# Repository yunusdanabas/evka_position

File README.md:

# Evka Position: Spherical 3D Positioning Prototype

> Turkce operator guide: [README_TR.md](README_TR.md)

Evka Position is an existing-repository prototype that derives a 3D point from two rotary
encoders and one draw-wire encoder:

```text
encoder counts -> (radius, theta, phi) -> sensor-frame (X, Y, Z) mm
```

Start with [HANDOFF.md](HANDOFF.md), use [docs/ONBOARDING.md](docs/ONBOARDING.md) for the
self-contained setup and safety baseline, and browse [docs/README.md](docs/README.md) for the
documentation status index.

## Handoff Status

| Area | Approved statement |
|---|---|
| Current hardware | The assembled ESP32-S3 v4 carrier is the current prototype. It is not a production-qualified product. |
| Firmware | Shared classic/v4 firmware and all PlatformIO environments build successfully. No new flash or hardware validation is claimed. |
| Telemetry | Live 20 Hz telemetry has been observed in earlier work. Full end-to-end hardware acceptance remains open. |
| Repeatability | Theta count loss is unresolved. The recorded return error reached about 1.1 degrees, approximately 35 mm at 2 m. |
| Coordinates | Firmware and `tools/evka_gui` report the sensor frame. No endpoint/world transform has been accepted. |
| Host application | `tools/evka_gui` is the canonical operator GUI. The vendor C# application has been deleted; the TCP compatibility protocol remains supported. |
| Legal/release | The repository has no redistribution license and makes no public production-readiness claim. |

Do not hide theta slip, backlash, or lost counts by changing PPR or fitting a world transform.
Resolve repeatability first, then calibrate scale, fit a candidate transform, and validate it on
hold-out points.

Known repeatability record:
[docs/calibration/sessions/2026-07-17_repeatability.md](docs/calibration/sessions/2026-07-17_repeatability.md).

### Software Verification Record

| Check | Result |
|---|---|
| `QT_QPA_PLATFORM=offscreen pytest -q -m qt_heavy --forked` | PASS: 44 tests |
| `QT_QPA_PLATFORM=offscreen pytest -q -m "not qt_heavy"` | PASS: 160 tests, 11 subtests (204 total with the above) |
| Dashboard harness (`npm ci && npm test`) | PASS: 50 checks |
| `python -m compileall tools -q` | PASS |
| `python -m tools.ipt.solver` | PASS: 0.405 mm target error |
| PlatformIO build matrix | PASS: all 10 configured environments |

The Python suite runs as **two invocations on purpose**. Modules marked `qt_heavy` build
pyqtgraph widgets that segfault when they share a process, so they run forked; forking only
works if the parent has not built a QApplication first, which is why they get their own
invocation. A plain `pytest -q` is still expected to segfault intermittently — use the two
commands above. Background: [docs/CI_PYTEST_SEGFAULT_LOG.md](docs/CI_PYTEST_SEGFAULT_LOG.md).

These are software-only results. Hardware acceptance remains governed by the open
gates in [docs/integration/final_integration_validation.md](docs/integration/final_integration_validation.md).

## Hardware Baseline

- MCU: ESP32-S3-DevKitC-1 on the v4 carrier; classic Wemos D1 R32 remains a compatibility target.
- Theta/Phi: Autonics E40S6-5000, 20,000 counts/rev at X4 quadrature.
- Radius: OPKON DWEM2 P2000, theoretical 8,000 counts/rev at X4 quadrature.
- Main firmware encoder driver: `madhephaestus/ESP32Encoder` using ESP32 PCNT.
- Encoder outputs are 5 V; the v4 carrier includes the signal dividers required by the ESP32.

### v4 Connector Map

| Connector | Axis | PCB pin order | GPIO |
|---|---|---|---|
| J1 | Draw-wire | `1=A, 2=GND, 3=B, 4=+5V` | A=7, B=8 |
| J2 | Phi | `1=+5V, 2=A, 3=GND, 4=B` | A=4, B=5 |
| J3 | Theta | `1=A, 2=GND, 3=B, 4=+5V` | A=9, B=10 |

Cable colors:

| Encoder | A | B | +5V | GND |
|---|---|---|---|---|
| E40S6 theta/phi | Black | White | Brown | Blue |
| DWEM2 draw-wire | Yellow | Green | Brown | White |

This connector order is derived from the v4 KiCad PCB/pad nets and the current firmware pin map.
It was **not physically reverified during this final documentation pass**. Verify the actual board
and cable before applying power.

Compile-time pins, calibration defaults, battery behavior, LED selection, and network constants
are defined in `firmware/src/SphericalSensor.h`. Runtime PPR values may be overridden by NVS, so
query `CONSTANTS` before a calibration session.

## Canonical Operator GUI

The host-tools package is version `0.2.1` and requires Python 3.10 or newer.

Install the Python dependencies from the repository root:

```bash
python3 -m venv .venv
source .venv/bin/activate
pip install -r requirements.txt
```

Run the canonical GUI:

```bash
python -m tools.evka_gui
python -m tools.evka_gui --serial /dev/ttyACM0 --baud 115200
python -m tools.evka_gui --tcp 192.168.1.50:8080
python -m tools.evka_gui --ws 192.168.1.50
python -m tools.evka_gui --replay frames.csv
```

`evka_gui` supports Serial, TCP, WebSocket, and replay; includes Quick IPT, diagnostics,
recording, snapshots, and the calibration-report workflow; and records raw sensor-frame data.
Software zero is a display/session offset only. The GUI does not apply an endpoint/world transform
to live telemetry, so its XYZ and IPT results remain in the sensor frame.

The standalone `tools/position_checker` entry points are legacy compatibility tools.

## Firmware Build and Flash

PlatformIO is the supported firmware toolchain. Build without uploading:

```bash
pio run -e esp32s3_v4
pio run -e wemos_d1_r32
pio run -e button_remote
```

Flash after wiring and safety review. Replace `/dev/ttyACM0` with the correct port
(`/dev/ttyUSB0` on some boards, `COMx` on Windows). Do not open the same port in two apps at once.

**Main device** (ESP32-S3 v4 carrier — current prototype):

```bash
pio run -e esp32s3_v4 --target upload --upload-port /dev/ttyACM0
pio device monitor -e esp32s3_v4
```

Classic Wemos compatibility target (not for the v4 carrier):

```bash
pio run -e wemos_d1_r32 --target upload --upload-port /dev/ttyUSB0
```

**Remote control** (ESP32-C3 pendant, ESP-NOW):

```bash
pio run -e button_remote --target upload --upload-port /dev/ttyACM0
pio device monitor -e button_remote
```

Bench-only pendant test firmware (own AP `REMOTE_TEST`, no ESP-NOW — see
[`tools/remote_tester/README.md`](tools/remote_tester/README.md)):

```bash
pio run -e button_remote_test --target upload --upload-port /dev/ttyACM0
```

The `test_*` environments use the classic Wemos pin map and must not be flashed onto the v4
carrier. See [CONTRIBUTING.md](CONTRIBUTING.md) and
[pcb_design/EVKA_position_v4/FIRMWARE.md](pcb_design/EVKA_position_v4/FIRMWARE.md) before any
flash or bring-up work.

## Protocol and Networking

The canonical, source-derived transport and command reference is
**[docs/PROTOCOL.md](docs/PROTOCOL.md)**. In summary:

- Serial: 115200 baud; machine-readable `DATA,...` at 20 Hz.
- WebSocket: `ws://<device>/ws`; `DATA,...` at 20 Hz.
- TCP: port 8080; separate `X...,Y...,Z...` and `SENSOR,...` lines at 20 Hz.
- `RAW_COUNTS` returns zero-relative counts, not absolute PCNT values.

The firmware's existing credentials and addresses are unchanged:

| Setting | Current value |
|---|---|
| AP SSID | `CMDCNC_EVKA` |
| AP password | `cmdcnc1234` |
| AP dashboard | `http://192.168.1.50` |
| TCP | `192.168.1.50:8080` |
| WebSocket | `ws://192.168.1.50/ws` |
| STA static profile | `192.168.1.84/24`, gateway `192.168.1.254` |
| STA default network | `WIFI_STA_DEFAULT_SSID` / `_PASS` in [firmware/src/SphericalSensor.h](firmware/src/SphericalSensor.h) — a specific shop-floor network; change before deploying elsewhere |

These fixed credentials and unauthenticated command channels are suitable only for an isolated,
trusted lab network. Do not expose the AP, TCP port, or WebSocket to an untrusted LAN or the public
internet. `WIFI_SET` changes stored STA credentials and reboots the device.

## Calibration Boundary

The active workflow is documented under [docs/calibration/](docs/calibration/). No shared/default
calibration JSON is checked in and no endpoint/world transform is accepted. After the repeatability,
calibration, and hold-out gates pass, a session JSON may be supplied explicitly to the legacy
visualizer with `--legacy-visualizer --calibration <session-calibration.json>`. The canonical
`tools/evka_gui` remains sensor-frame-only.

## Repository Areas

- Active: `firmware/src/`, `tools/evka_gui/`, `docs/PROTOCOL.md`, active calibration and v4 docs.
- Archive/reference: classic test material, integration history, GUI migration logs, and
  `docs/hardware_design/12v_legacy/`.
- Research: `laser_radius/` and `docs/research/`; these are studies, not implemented baseline.
- Unindexed: `report/` holds a standalone LaTeX report that nothing else references. It is kept
  for the record and is not part of the documentation status index.

Prebuilt operator GUI bundles (Windows `.exe` and portable source) are published as assets on the
[v0.2.1 release](https://github.com/yunusdanabas/evka_position/releases/tag/v0.2.1), not in git.
Rebuild them with the scripts in `packaging/evka_gui/`.

## License and Redistribution

There is no repository license file. Default copyright restrictions apply. Do not redistribute,
publish a product release, or represent this prototype as production-ready until ownership and
licensing are explicitly resolved. Historical vendor C# material has been deleted; that cleanup does
not affect the retained TCP wire protocol.

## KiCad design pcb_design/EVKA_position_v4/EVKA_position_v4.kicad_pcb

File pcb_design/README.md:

# pcb_design — KiCad workspaces

Four board revisions live side by side. **Only v4 is fabricated and current** —
the rest are kept for reference.

| Workspace | Status | Notes |
|---|---|---|
| `EVKA_position_v4/` | **CURRENT — fabricated** | ESP32-S3-DevKitC-1 carrier; firmware env `esp32s3_v4` (`-DPCB_V4`). Pin map, bring-up, battery, LED: [`EVKA_position_v4/FIRMWARE.md`](EVKA_position_v4/FIRMWARE.md) |
| `EvkaPosition_v2/` | Superseded | Full-featured 5V design (74HC14 buffers, load-sharing). ERC-clean but never fabricated. Its design docs were removed on migration to v4 — recover from git history if needed |
| `EVKA_position_v3/` | Superseded | Stripped "simple" variant of v2 (direct-GPIO dividers, no buffers). Never fabricated |
| `EVKA_position_v5/` | Experimental / WIP | Layout exploration after v4; not fabricated, no firmware support |

Netlists are generated files — regenerate with
`kicad-cli sch export netlist <project>.kicad_sch` (a stray root-level
`EvkaPosition_v2.net` is git-ignored for this reason). KiCad backup folders
(`*-backups/`) are git-ignored too.

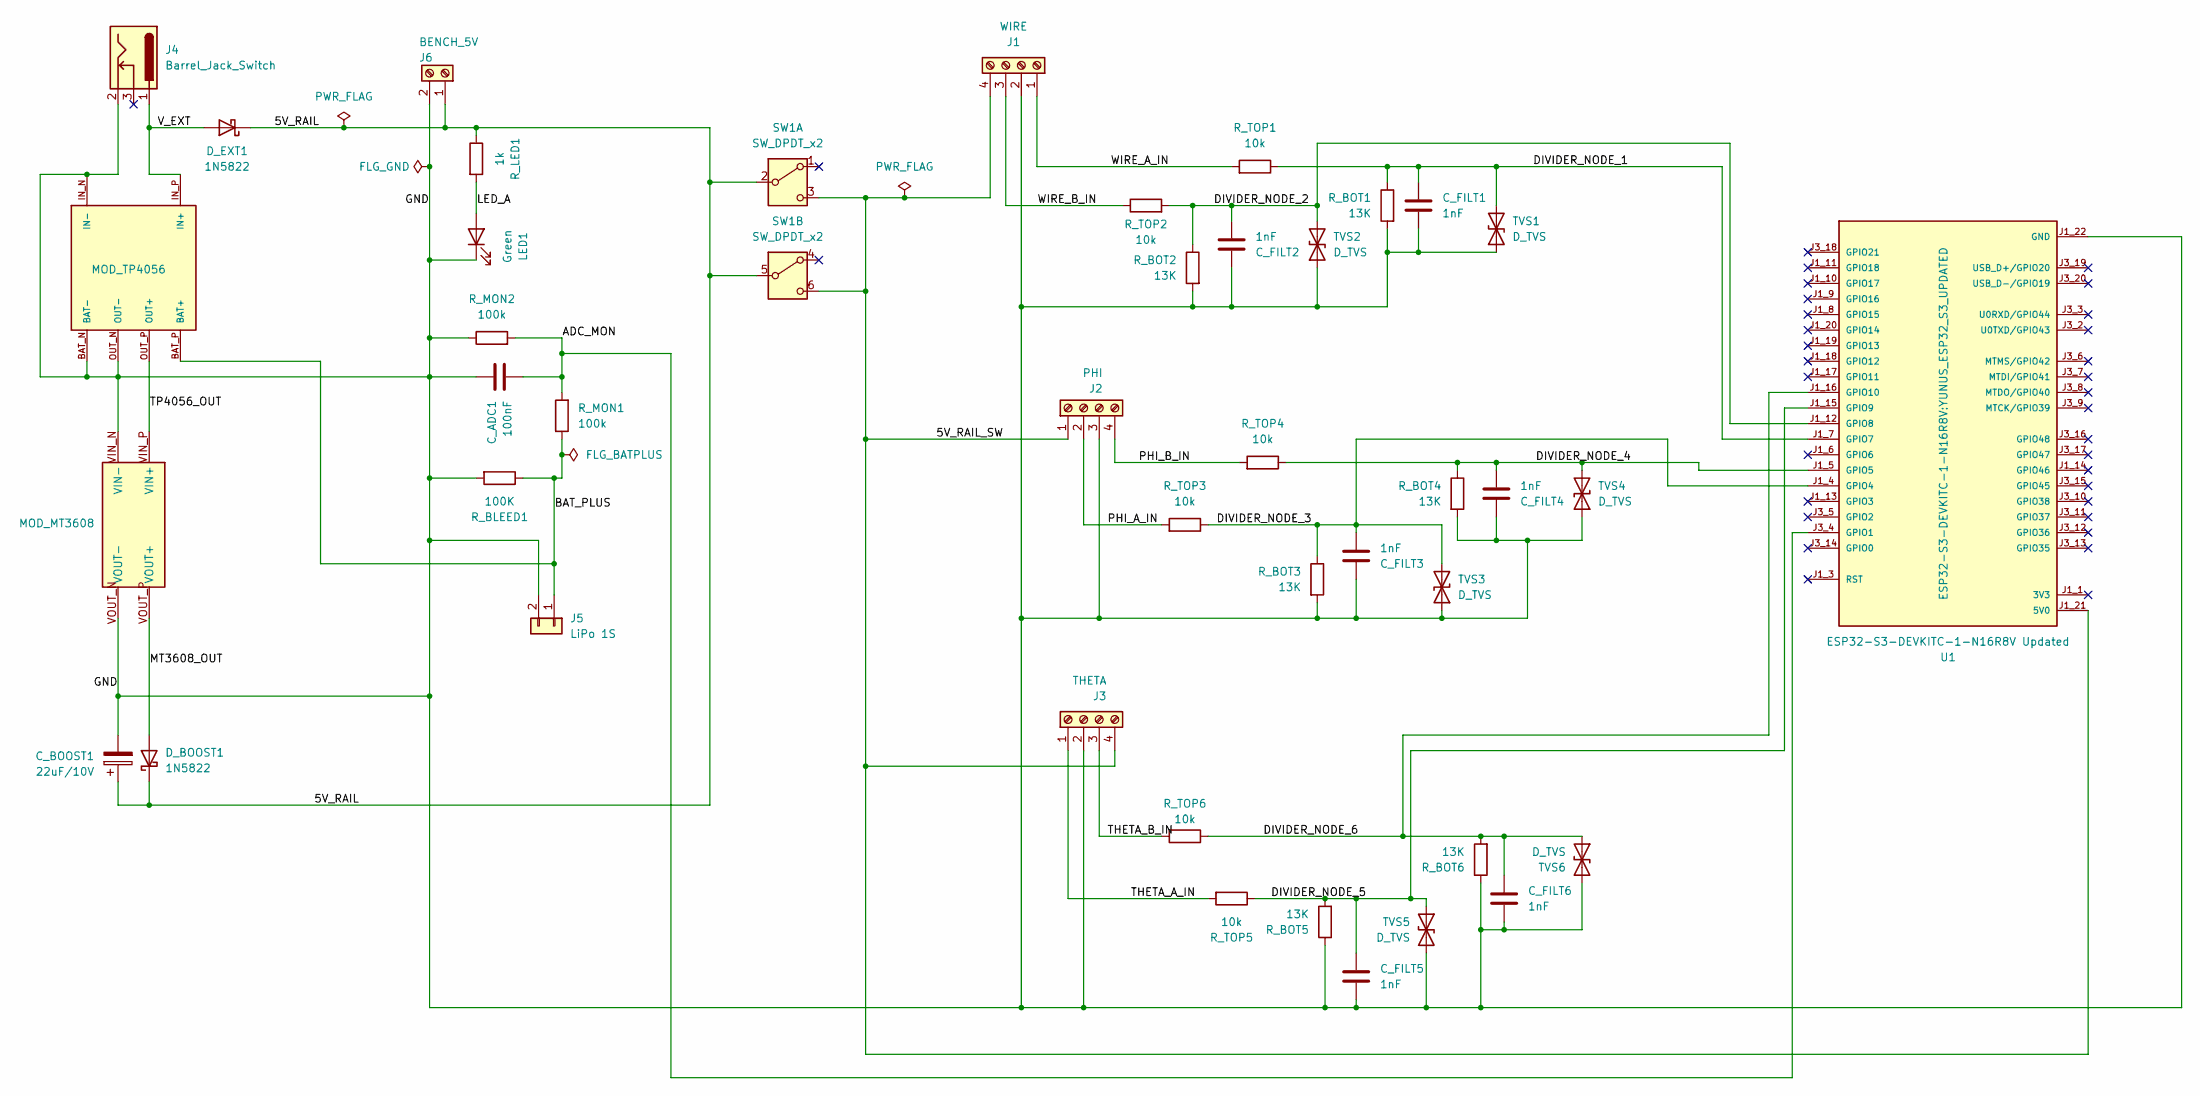
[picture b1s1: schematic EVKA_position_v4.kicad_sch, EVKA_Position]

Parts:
C_ADC1: 100nF; C_Disc_D5.0mm_W2.5mm_P5.00mm
C_BOOST1: 22uF/10V; CP_Radial_D5.0mm_P2.50mm
C_FILT1, C_FILT2, C_FILT3, C_FILT4, C_FILT5, C_FILT6: 1nF; C_Disc_D5.0mm_W2.5mm_P5.00mm
D_BOOST1: 1N5822; D_DO-201AD_P15.24mm_Horizontal
D_EXT1: 1N5822; D_DO-201AD_P15.24mm_Horizontal
J1: WIRE; TerminalBlock_Phoenix_MKDS-1,5-4_1x04_P5.00mm_Horizontal
J2: PHI; TerminalBlock_Phoenix_MKDS-1,5-4_1x04_P5.00mm_Horizontal
J3: THETA; TerminalBlock_Phoenix_MKDS-1,5-4_1x04_P5.00mm_Horizontal
J4: Barrel_Jack_Switch; BarrelJack_CUI_PJ-102AH_Horizontal
J5: LiPo 1S; JST_PH_B2B-PH-K_1x02_P2.00mm_Vertical
J6: BENCH_5V; TerminalBlock_Phoenix_MKDS-1,5-2_1x02_P5.00mm_Horizontal
LED1: Green; LED_D5.0mm
MOD_MT3608: MT3608 Updated; MODULE_MT3608_DC-DC_STEP_UP_CONVERTER_2A_BOOSTER_MODULE
MOD_TP4056: TP4056_MICRO-USB_CHARGER_-_1A; MODULE_TP4056_MICRO-USB_CHARGER_-_1A
R_BLEED1: 100K; R_Axial_DIN0207_L6.3mm_D2.5mm_P7.62mm_Horizontal
R_BOT1, R_BOT2, R_BOT3, R_BOT4, R_BOT5, R_BOT6: 13K; R_Axial_DIN0207_L6.3mm_D2.5mm_P7.62mm_Horizontal
R_LED1: 1k; R_Axial_DIN0207_L6.3mm_D2.5mm_P7.62mm_Horizontal
R_MON1, R_MON2: 100k; R_Axial_DIN0207_L6.3mm_D2.5mm_P7.62mm_Horizontal
R_TOP1, R_TOP2, R_TOP3, R_TOP4, R_TOP5, R_TOP6: 10k; R_Axial_DIN0207_L6.3mm_D2.5mm_P7.62mm_Horizontal
SW1: SW_DPDT_x2; SW_NKK_G1xJP
TVS1, TVS2, TVS3, TVS4, TVS5, TVS6: D_TVS; D_DO-35_SOD27_P7.62mm_Horizontal
U1: ESP32-S3-DEVKITC-1-N16R8V Updated; YUNUS_ESP32_S3_UPDATED; PARTREV 1.1

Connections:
/5V_RAIL: C_BOOST1.1, D_BOOST1.1 (K), D_EXT1.1 (K), J6.1, R_LED1.1, SW1.2 (B), SW1.5 (B)
/5V_RAIL_SW: J1.4, J2.1, J3.4, SW1.3 (C), SW1.6 (C), U1.J1_21 (5V0)
/ADC_MON: C_ADC1.2, R_MON1.2, R_MON2.2, U1.J3_4 (GPIO1)
/BAT_PLUS: J5.1, MOD_TP4056.BAT_P (BAT+), R_BLEED1.1, R_MON1.1
/DIVIDER_NODE_1: C_FILT1.1, R_BOT1.1, R_TOP1.1, TVS1.2 (A2), U1.J1_7 (GPIO7)
/DIVIDER_NODE_2: C_FILT2.2, R_BOT2.1, R_TOP2.2, TVS2.2 (A2), U1.J1_12 (GPIO8)
/DIVIDER_NODE_3: C_FILT3.2, R_BOT3.1, R_TOP3.1, TVS3.2 (A2), U1.J1_4 (GPIO4)
/DIVIDER_NODE_4: C_FILT4.2, R_BOT4.1, R_TOP4.1, TVS4.2 (A2), U1.J1_5 (GPIO5)
/DIVIDER_NODE_5: C_FILT5.1, R_BOT5.2, R_TOP5.1, TVS5.1 (A1), U1.J1_15 (GPIO9)
/DIVIDER_NODE_6: C_FILT6.1, R_BOT6.2, R_TOP6.1, TVS6.1 (A1), U1.J1_16 (GPIO10)
/LED_A: LED1.2 (A), R_LED1.2
/MT3608_OUT: D_BOOST1.2 (A), MOD_MT3608.VOUT_P (VOUT+)
/PHI_A_IN: J2.2, R_TOP3.2
/PHI_B_IN: J2.4, R_TOP4.2
/THETA_A_IN: J3.1, R_TOP5.2
/THETA_B_IN: J3.3, R_TOP6.2
/TP4056_OUT: MOD_MT3608.VIN_P (VIN+), MOD_TP4056.OUT_P (OUT+)
/V_EXT: D_EXT1.2 (A), J4.1, MOD_TP4056.IN_P (IN+)
/WIRE_A_IN: J1.1, R_TOP1.2
/WIRE_B_IN: J1.3, R_TOP2.1
GND: C_ADC1.1, C_BOOST1.2, C_FILT1.2, C_FILT2.1, C_FILT3.1, C_FILT4.1, C_FILT5.2, C_FILT6.2, J1.2, J2.3, J3.2, J4.2, J5.2, J6.2, LED1.1 (K), MOD_MT3608.VIN_N (VIN-), MOD_MT3608.VOUT_N (VOUT-), MOD_TP4056.BAT_N (BAT-), MOD_TP4056.IN_N (IN-), MOD_TP4056.OUT_N (OUT-), R_BLEED1.2, R_BOT1.2, R_BOT2.2, R_BOT3.2, R_BOT4.2, R_BOT5.1, R_BOT6.1, R_MON2.1, TVS1.1 (A1), TVS2.1 (A1), TVS3.1 (A1), TVS4.1 (A1), TVS5.2 (A2), TVS6.2 (A2), U1.J1_22 (GND), U1.J3_1 (GND), U1.J3_21 (GND), U1.J3_22 (GND)

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
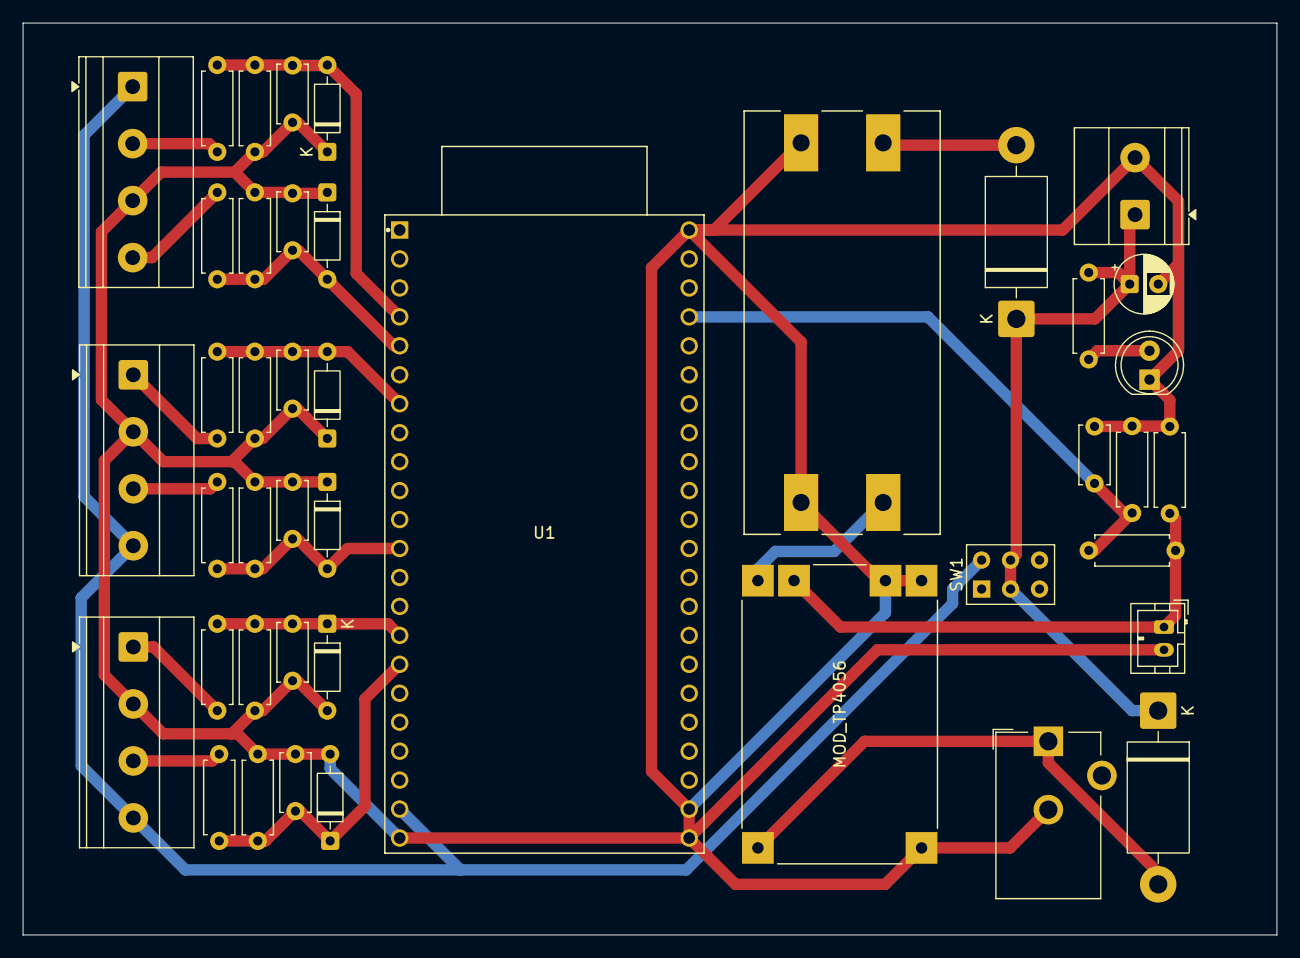
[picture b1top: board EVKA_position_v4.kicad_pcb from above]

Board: 2 copper layers, 110.0 x 80.0 mm, 43 parts (0 on the bottom side), 21 nets.

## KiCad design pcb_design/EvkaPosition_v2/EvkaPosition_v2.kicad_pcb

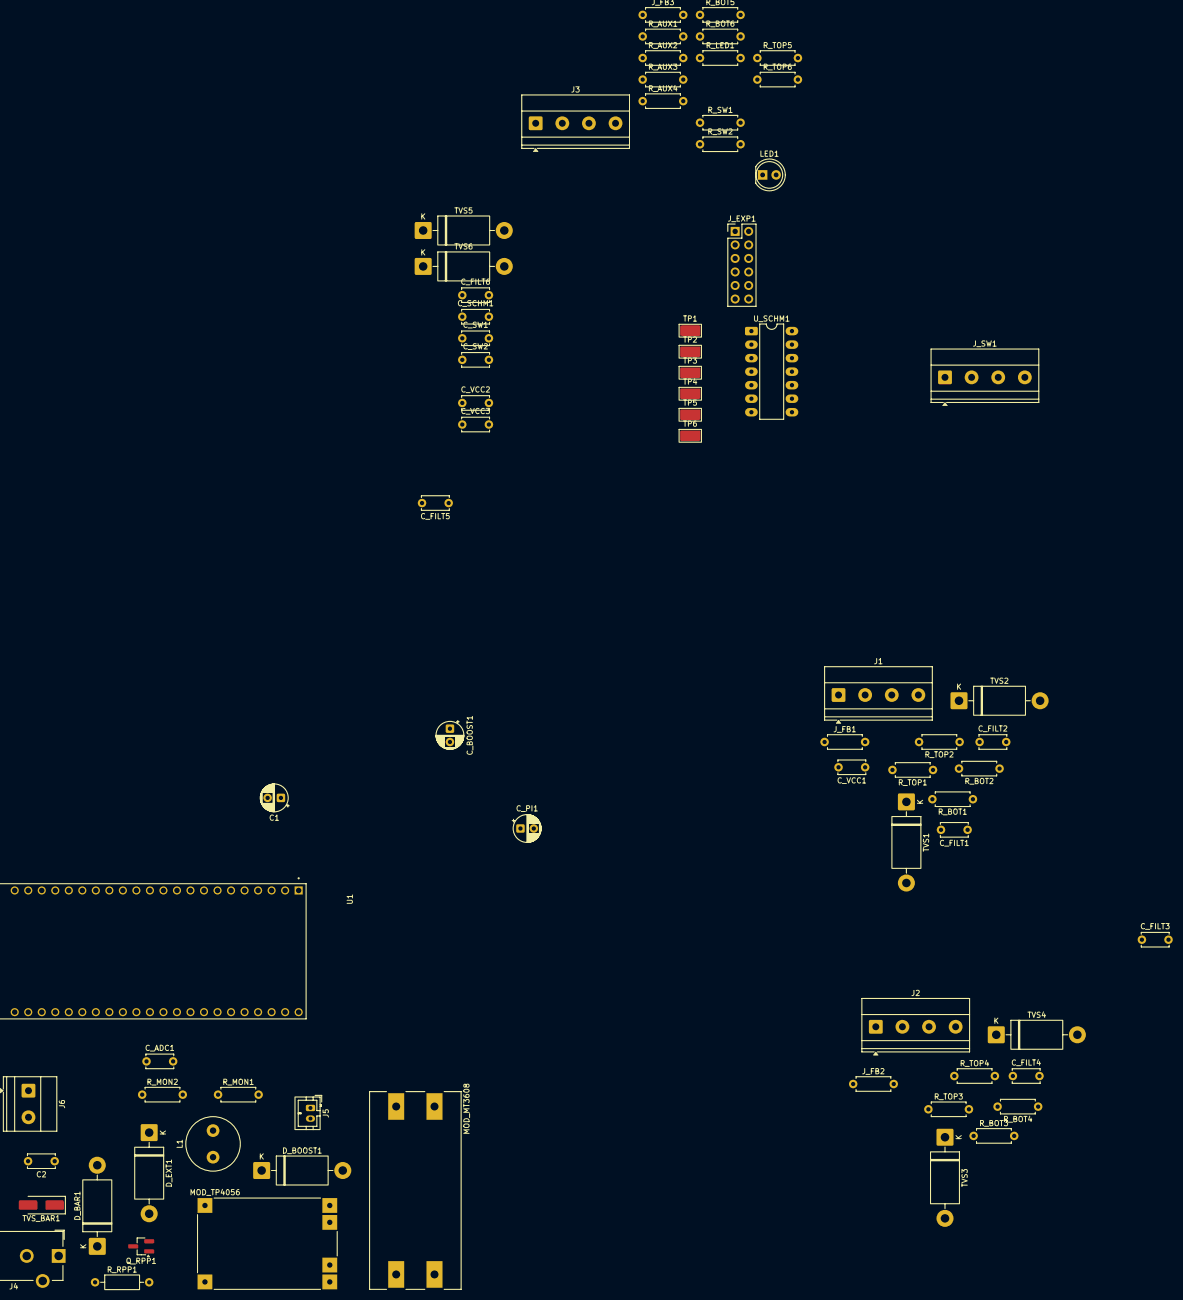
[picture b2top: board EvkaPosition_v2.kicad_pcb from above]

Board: 2 copper layers, 73 parts (0 on the bottom side), 44 nets, no tracks yet.

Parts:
C1: 220uF/10V; CP_Radial_D5.0mm_P2.50mm
C2: 100nF; C_Disc_D5.0mm_W2.5mm_P5.00mm
C_ADC1: 100nF; C_Disc_D5.0mm_W2.5mm_P5.00mm
C_BOOST1: 22uF/10V; CP_Radial_D5.0mm_P2.50mm
C_FILT1, C_FILT2, C_FILT3, C_FILT4, C_FILT5, C_FILT6: 10nF; C_Disc_D5.0mm_W2.5mm_P5.00mm
C_PI1: 10uF/10V; CP_Radial_D5.0mm_P2.50mm
C_SCHM1: 100nF; C_Disc_D5.0mm_W2.5mm_P5.00mm
C_SW1, C_SW2: 100nF; C_Disc_D5.0mm_W2.5mm_P5.00mm
C_VCC1, C_VCC2, C_VCC3: 100nF; C_Disc_D5.0mm_W2.5mm_P5.00mm
D_BAR1: 1N5822; D_DO-201AD_P15.24mm_Horizontal
D_BOOST1: 1N5822; D_DO-201AD_P15.24mm_Horizontal
D_EXT1: 1N5822; D_DO-201AD_P15.24mm_Horizontal
J1: THETA; TerminalBlock_Phoenix_MKDS-1,5-4_1x04_P5.00mm_Horizontal
J2: PHI; TerminalBlock_Phoenix_MKDS-1,5-4_1x04_P5.00mm_Horizontal
J3: WIRE; TerminalBlock_Phoenix_MKDS-1,5-4_1x04_P5.00mm_Horizontal
J4: Barrel_Jack_Switch; BarrelJack_CUI_PJ-102AH_Horizontal
J5: LiPo 1S; JST_PH_B2B-PH-K_1x02_P2.00mm_Vertical
J6: BENCH_5V; TerminalBlock_Phoenix_MKDS-1,5-2_1x02_P5.00mm_Horizontal
J_EXP1: AUX_IO; PinHeader_2x06_P2.54mm_Vertical
J_FB1, J_FB2, J_FB3: 0R; R_Axial_DIN0207_L6.3mm_D2.5mm_P7.62mm_Horizontal
J_SW1: SWITCHES; TerminalBlock_Phoenix_MKDS-1,5-4_1x04_P5.00mm_Horizontal
L1: 10uH; L_Radial_D10.0mm_P5.00mm_Neosid_SD12_style3
LED1: Green; LED_D5.0mm
MOD_MT3608: MT3608_DC-DC_STEP_UP_CONVERTER_2A_BOOSTER_MODULE; MODULE_MT3608_DC-DC_STEP_UP_CONVERTER_2A_BOOSTER_MODULE
MOD_TP4056: TP4056_MICRO-USB_CHARGER_-_1A; MODULE_TP4056_MICRO-USB_CHARGER_-_1A
Q_RPP1: PJA3441; SOT-23_Handsoldering
R_AUX1, R_AUX2, R_AUX3, R_AUX4: 100R; R_Axial_DIN0207_L6.3mm_D2.5mm_P7.62mm_Horizontal
R_BOT1, R_BOT2, R_BOT3, R_BOT4, R_BOT5, R_BOT6: 20k; R_Axial_DIN0207_L6.3mm_D2.5mm_P7.62mm_Horizontal
R_LED1: 1k; R_Axial_DIN0207_L6.3mm_D2.5mm_P7.62mm_Horizontal
R_MON1, R_MON2: 100k; R_Axial_DIN0207_L6.3mm_D2.5mm_P7.62mm_Horizontal
R_RPP1: 100k; R_Axial_DIN0207_L6.3mm_D2.5mm_P10.16mm_Horizontal
R_SW1, R_SW2: 10k; R_Axial_DIN0207_L6.3mm_D2.5mm_P7.62mm_Horizontal
R_TOP1, R_TOP2, R_TOP3, R_TOP4, R_TOP5, R_TOP6: 10k; R_Axial_DIN0207_L6.3mm_D2.5mm_P7.62mm_Horizontal
TP1: 5V_RAIL; TestPoint_Keystone_5019_Miniature
TP2: 3V3; TestPoint_Keystone_5019_Miniature
TP3: MT3608_OUT; TestPoint_Keystone_5019_Miniature
TP4: BAT+; TestPoint_Keystone_5019_Miniature
TP5: BAT_OUT; TestPoint_Keystone_5019_Miniature
TP6: GND; TestPoint_Keystone_5019_Miniature
TVS1, TVS2, TVS3, TVS4, TVS5, TVS6: D_TVS; D_DO-201AD_P15.24mm_Horizontal
TVS_BAR1: SMAJ5.0A; D_SMA_Handsoldering
U1: ESP32-S3-DEVKITC-1-N16R8V; XCVR_ESP32-S3-DEVKITC-1-N16R8V
U_SCHM1: 74HC14; DIP-14_W7.62mm_LongPads

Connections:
3V3: C_SCHM1.2, J_EXP1.9, J_SW1.4, R_SW1.2, R_SW2.2, TP2.1 (1_1), U1.J1_1 (3V3), U1.J1_2 (3V3), U_SCHM1.14 (VCC)
/+5V: C1.1, C2.1, J6.1, J_EXP1.11, J_FB1.1, J_FB2.1, J_FB3.2, L1.2, R_LED1.1, TP1.1 (1_1), U1.J1_21 (5V0)
/ADC_MON: C_ADC1.2, R_MON1.1, R_MON2.2, U1.J3_4 (GPIO1)
/AUX1: J_EXP1.1, R_AUX1.2
/AUX2: J_EXP1.3, R_AUX2.2
/AUX3: J_EXP1.5, R_AUX3.2
/AUX4: J_EXP1.7, R_AUX4.2
/BAT_OUT: MOD_MT3608.VIN_P (VIN+), MOD_TP4056.OUT_P (OUT+), TP5.1 (1_1)
/BAT_PLUS: J5.1, MOD_TP4056.BAT_P (BAT+), R_MON1.2, TP4.1 (1_1)
/BTN1: C_SW1.2, J_SW1.2, R_SW1.1, U1.J1_10 (GPIO17)
/BTN2: C_SW2.2, J_SW1.3, R_SW2.1, U1.J1_11 (GPIO18)
/DIVIDER_NODE_1: C_FILT1.2, R_BOT1.2, R_TOP1.1, TVS1.1 (A1), U_SCHM1.1
/DIVIDER_NODE_2: C_FILT2.1, R_BOT2.2, R_TOP2.1, TVS2.1 (A1), U_SCHM1.3
/DIVIDER_NODE_3: C_FILT3.1, R_BOT3.2, R_TOP3.1, TVS3.1 (A1), U_SCHM1.9
/DIVIDER_NODE_4: C_FILT4.1, R_BOT4.2, R_TOP4.1, TVS4.1 (A1), U_SCHM1.5
/DIVIDER_NODE_5: C_FILT5.1, R_BOT5.2, R_TOP5.1, TVS5.1 (A1), U_SCHM1.11
/DIVIDER_NODE_6: C_FILT6.1, R_BOT6.2, R_TOP6.1, TVS6.1 (A1), U_SCHM1.13
/ENC_VCC1: C_VCC1.1, J1.2, J_FB1.2
/ENC_VCC2: C_VCC2.1, J2.2, J_FB2.2
/ENC_VCC3: C_VCC3.1, J3.2, J_FB3.1
/LED_A: LED1.2 (A), R_LED1.2
/MT3608_OUT: C_BOOST1.1, D_BOOST1.2 (A), MOD_MT3608.VOUT_P (VOUT+), TP3.1 (1_1)
/PHI_A_IN: J2.3, R_TOP3.2
/PHI_A_OUT: U1.J1_6 (GPIO6), U_SCHM1.8
/PHI_B_IN: J2.4, R_TOP4.2
/PHI_B_OUT: U1.J1_7 (GPIO7), U_SCHM1.6
/PI_NODE: C_PI1.1, D_BOOST1.1 (K), D_EXT1.1 (K), L1.1
/RPP_GATE: Q_RPP1.1 (G), R_RPP1.2
/THETA_A_IN: J1.3, R_TOP1.2
/THETA_A_OUT: U1.J1_4 (GPIO4), U_SCHM1.2
/THETA_B_IN: J1.4, R_TOP2.2
/THETA_B_OUT: U1.J1_5 (GPIO5), U_SCHM1.4
/V_EXT_PROT: D_EXT1.2 (A), MOD_TP4056.IN_P (IN+), Q_RPP1.2 (S)
/V_EXT_RAW: D_BAR1.1 (K), Q_RPP1.3 (D)
/V_IN_JACK: D_BAR1.2 (A), J4.1, TVS_BAR1.1 (A1)
/WIRE_A_IN: J3.3, R_TOP5.2
/WIRE_A_OUT: U1.J1_8 (GPIO15), U_SCHM1.10
/WIRE_B_IN: J3.4, R_TOP6.2
/WIRE_B_OUT: U1.J1_9 (GPIO16), U_SCHM1.12
GND: C1.2, C2.2, C_ADC1.1, C_BOOST1.2, C_FILT1.1, C_FILT2.2, C_FILT3.2, C_FILT4.2, C_FILT5.2, C_FILT6.2, C_PI1.2, C_SCHM1.1, C_SW1.1, C_SW2.1, C_VCC1.2, C_VCC2.2, C_VCC3.2, J1.1, J2.1, J3.1, J4.2, J5.2, J6.2, J_EXP1.2, J_EXP1.4, J_EXP1.6, J_EXP1.8, J_EXP1.10, J_EXP1.12, J_SW1.1, LED1.1 (K), MOD_MT3608.VIN_N (VIN-), MOD_MT3608.VOUT_N (VOUT-), MOD_TP4056.BAT_N (BAT-), MOD_TP4056.IN_N (IN-), MOD_TP4056.OUT_N (OUT-), R_BOT1.1, R_BOT2.1, R_BOT3.1, R_BOT4.1, R_BOT5.1, R_BOT6.1, R_MON2.1, R_RPP1.1, TP6.1 (1_1), TVS1.2 (A2), TVS2.2 (A2), TVS3.2 (A2), TVS4.2 (A2), TVS5.2 (A2), TVS6.2 (A2), TVS_BAR1.2 (A2), U1.J1_22 (GND), U1.J3_1 (GND), U1.J3_21 (GND), U1.J3_22 (GND), U_SCHM1.7 (GND)
unnamed: R_AUX1.1, U1.J1_17 (GPIO11)
unnamed: R_AUX2.1, U1.J1_18 (GPIO12)
unnamed: R_AUX3.1, U1.J1_19 (GPIO13)
unnamed: R_AUX4.1, U1.J1_20 (GPIO14)

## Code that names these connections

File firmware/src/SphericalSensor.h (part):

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// EVKA_position_v4 — ESP32-S3-DevKitC-1. Encoders via on-board 10k/20k dividers
// straight to GPIO (no Schmitt buffer). Verified against the v4 schematic AND PCB
// pad-nets (WIRE=DIVIDER_NODE_1/2 on J1, PHI=_3/4 on J2, THETA=_5/6 on J3).
// GPIO17/18 are NOT wired.
#define PIN_THETA_A   9     // DIVIDER_NODE_5 (J3.1 theta A)
#define PIN_THETA_B   10    // DIVIDER_NODE_6 (J3.3 theta B)
#define PIN_PHI_A     4     // DIVIDER_NODE_3 (J2.2 phi A)
#define PIN_PHI_B     5     // DIVIDER_NODE_4 (J2.4 phi B)
#define PIN_WIRE_A    7     // DIVIDER_NODE_1 (J1.1 wire A)
#define PIN_WIRE_B    8     // DIVIDER_NODE_2 (J1.3 wire B)
#else
// Classic ESP32 (Wemos D1 R32). Must stay interrupt/PCNT-capable.
#define PIN_THETA_A   14    // Encoder pin (Theta azimuth axis)
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#endif
#define PIN_WIFI_LED     2   // GPIO 2 = built-in LED on classic ESP32 boards

// Battery / supply monitoring (ADC1_CH0). v4: GPIO1 (1S divider); classic: GPIO36.
#if defined(PCB_V4)
#define PIN_BATTERY_ADC  1    // GPIO 1 (ADC1_CH0) — 100k/100k divider on 1S LiPo
#else
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
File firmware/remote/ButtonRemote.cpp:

// ============================================================================
// EvkaPosition — Wireless Button Remote (ESP-NOW Sender)
// ============================================================================
// Target: ESP32-C3 (Seeed XIAO ESP32-C3 or ESP32-C3 SuperMini)
// Always-awake mode: ESP-NOW initialised once at startup.
// Sends a single byte (button index 0–4) on each confirmed press edge.
//
// Button wiring: Each button connects GPIO → GND (internal pull-up enabled).
// ============================================================================

#include <Arduino.h>
#include <esp_now.h>
#include <esp_wifi.h>
#include <WiFi.h>

// ============================================================================
// CONFIGURATION
// ============================================================================

#define FIRMWARE_VERSION "ButtonRemote v1.1"

// Number of buttons and GPIO assignments.
// Safe GPIOs on ESP32-C3: avoids strapping pins (2, 9), serial (6, 7), LED (8).
#define BTN_COUNT     5

// LED feedback pin — GPIO 8 = built-in blue LED on ESP32-C3 SuperMini
#define PIN_LED       8

// WiFi channel — fallback if AP scan fails
#define ESPNOW_CHANNEL   1
// Main ESP32 AP SSID — scanned at startup to find the actual WiFi channel
#define MAIN_AP_SSID    "CMDCNC_EVKA"
#define SCAN_RETRIES     3
// Lower TX power reduces WiFi current peaks on weak Type-C/extension supplies.
#define REMOTE_WIFI_TX_POWER WIFI_POWER_8_5dBm

// Heartbeat
#define HEARTBEAT_INTERVAL_MS  10000
#define HEARTBEAT_BYTE         0xFE

// Debounce
#define DEBOUNCE_MS   50
// Ignore buttons for the first 500 ms: GPIO 0 may read LOW while the
// USB-JTAG bridge is still settling after reset.
#define BOOT_GUARD_MS 500

// ============================================================================
// INTERNALS
// ============================================================================

// BTN0=GPIO4 (Green/SAVE_POINT), BTN1=GPIO5 (Red/DEL_POINT),
// BTN2=GPIO0, BTN3=GPIO1, BTN4=GPIO3
static const uint8_t BTN_PINS[BTN_COUNT] = {4, 5, 0, 1, 3};

struct ButtonState {
    bool     last_raw;        // last raw digitalRead() result (true = pressed = LOW)
    bool     confirmed;       // debounce-settled state
    uint32_t last_change_ms;  // millis() of last raw edge
};
static ButtonState g_buttons[BTN_COUNT];

static uint8_t broadcast_addr[] = { 0xFF, 0xFF, 0xFF, 0xFF, 0xFF, 0xFF };

static volatile bool send_done = false;
static volatile bool send_ok   = false;

static void onSendDone(const uint8_t* mac, esp_now_send_status_t status) {
    send_ok   = (status == ESP_NOW_SEND_SUCCESS);
    send_done = true;
}

static void ledOn()  { digitalWrite(PIN_LED, HIGH); }
static void ledOff() { digitalWrite(PIN_LED, LOW);  }

static void initButtons() {
    for (uint8_t i = 0; i < BTN_COUNT; i++) {
        pinMode(BTN_PINS[i], INPUT_PULLUP);
        g_buttons[i] = {false, false, 0};
    }
}

// ============================================================================
// SETUP — runs once at power-on
// ============================================================================

void setup() {
    Serial.begin(115200);
    delay(500);

    Serial.println(FIRMWARE_VERSION);
    Serial.println("[ButtonRemote] ESP-NOW wireless pendant (always-awake)");

    initButtons();
    pinMode(PIN_LED, OUTPUT);
    ledOff();

    // Initialise WiFi in STA mode, prevent any auto-scan/reconnect,
    // then pin to the ESP-NOW channel before initialising the stack.
    WiFi.mode(WIFI_STA);
    if (!WiFi.setTxPower(REMOTE_WIFI_TX_POWER)) {
        Serial.println("[ButtonRemote] WARN: setTxPower failed");
    } else {
        Serial.println("[ButtonRemote] TX power set to WIFI_POWER_8_5dBm");
    }
    WiFi.setAutoReconnect(false);
    WiFi.disconnect(false, true);   // disconnect + erase stored AP credentials
    delay(100);                     // let WiFi stack settle before channel change

    // Scan for the main ESP32's AP to discover its current WiFi channel.
    // When the main board's STA connects to a home router on channel != 1,
    // its AP silently moves to that channel — hardcoding ch1 would break ESP-NOW.
    uint8_t active_channel = ESPNOW_CHANNEL;  // fallback
    bool found_ap = false;
    for (int attempt = 0; attempt < SCAN_RETRIES; attempt++) {
        if (attempt > 0) delay(1000);
        Serial.printf("[ButtonRemote] Scanning for '%s'... (attempt %d/%d)\n",
                      MAIN_AP_SSID, attempt + 1, SCAN_RETRIES);
        int n = WiFi.scanNetworks(false, false, false, 200);
        for (int i = 0; i < n; i++) {
            if (WiFi.SSID(i) == MAIN_AP_SSID) {
                active_channel = (uint8_t)WiFi.channel(i);
                found_ap = true;
                Serial.printf("[ButtonRemote] Found on ch%u (RSSI %d dBm)\n",
                              active_channel, WiFi.RSSI(i));
                break;
            }
        }
        WiFi.scanDelete();
        if (found_ap) break;
    }
    if (!found_ap) {
        Serial.printf("[ButtonRemote] AP not found — using fallback ch%u\n", active_channel);
    }

    esp_err_t ch_err = esp_wifi_set_channel(active_channel, WIFI_SECOND_CHAN_NONE);
    Serial.printf("[ButtonRemote] Channel set ch%u -> %s\n",
                  active_channel, ch_err == ESP_OK ? "OK" : "FAIL");

    // Initialise ESP-NOW once — stays active for the lifetime of the device
    if (esp_now_init() != ESP_OK) {
        Serial.println("[ButtonRemote] ESP-NOW init FAILED");
        return;
    }
    esp_now_register_send_cb(onSendDone);

    esp_now_peer_info_t peer = {};
    memcpy(peer.peer_addr, broadcast_addr, 6);
    peer.channel = active_channel;
    peer.encrypt = false;
    esp_now_add_peer(&peer);

    Serial.println("[ButtonRemote] ESP-NOW ready");
    Serial.println("[ButtonRemote] Waiting for button press...");
    Serial.println("  BTN0 GPIO4 -> SAVE_POINT (Green - Add Point)");
    Serial.println("  BTN1 GPIO5 -> DEL_POINT  (Red   - Delete Last Point)");
    Serial.println("  BTN2 GPIO0 -> (unassigned)");
    Serial.println("  BTN3 GPIO1 -> (unassigned)");
    Serial.println("  BTN4 GPIO3 -> (unassigned)");
}

// ============================================================================
// LOOP — runs continuously
// ============================================================================

void loop() {
    // Heartbeat — keeps the link-status indicator alive on the host GUIs.
    // Sends 0xFE every HEARTBEAT_INTERVAL_MS; main ESP32 rebroadcasts as REMOTE_HB.
    static unsigned long last_hb_ms = 0;
    if (millis() - last_hb_ms >= HEARTBEAT_INTERVAL_MS) {
        last_hb_ms = millis();
        uint8_t hb = HEARTBEAT_BYTE;
        send_done = false; send_ok = false;
        esp_now_send(broadcast_addr, &hb, 1);
        unsigned long t0 = millis();
        while (!send_done && (millis() - t0) < 100) delay(1);
        Serial.printf("[ButtonRemote] Heartbeat -> %s\n", send_ok ? "OK" : "FAIL");
    }

    // Per-button debounce — fires exactly once per confirmed press edge.
    // Boot guard prevents false triggers from GPIO 0 floating LOW at reset.
    if (millis() >= BOOT_GUARD_MS) {
        for (uint8_t i = 0; i < BTN_COUNT; i++) {
            bool raw = (digitalRead(BTN_PINS[i]) == LOW);  // true = pressed

            // Detect raw edge and restart settle timer
            if (raw != g_buttons[i].last_raw) {
                g_buttons[i].last_raw       = raw;
                g_buttons[i].last_change_ms = millis();
            }

            // Commit only when raw has been stable for DEBOUNCE_MS
            if ((millis() - g_buttons[i].last_change_ms) >= DEBOUNCE_MS) {
                if (raw != g_buttons[i].confirmed) {
                    g_buttons[i].confirmed = raw;

                    if (raw) {
                        // Confirmed press edge — send button index via ESP-NOW
                        Serial.printf("[ButtonRemote] Button %d pressed — sending...\n", i);
                        ledOn();

                        uint8_t payload = i;
                        send_done = false;
                        send_ok   = false;
                        esp_now_send(broadcast_addr, &payload, 1);

                        // Wait for send callback (max 100 ms)
                        unsigned long t0 = millis();
                        while (!send_done && (millis() - t0) < 100) {
                            delay(1);
                        }

                        if (send_ok) {
                            Serial.println("[ButtonRemote] Send OK");
                            delay(80);   // brief solid LED = success
                        } else {
                            // Quick blink = fail
                            ledOff(); delay(50); ledOn(); delay(50); ledOff(); delay(50);
                            Serial.println("[ButtonRemote] Send FAILED");
                        }
                        ledOff();
                    }
                }
            }
        }
    }
}

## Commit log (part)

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2026-02-26 Phase 4: PPR correction, .ino->.cpp migration, repo cleanup
    - Update PPR_ROTARY from datasheet 5000 to measured 1480
    - Migrate all firmware from .ino to .cpp for PlatformIO
    - Restructure tests from firmware/tests/ to firmware/
    - Add SingleRotaryTest for individual encoder testing
    - Remove GEMINI.md (redundant), move test plan to docs/
    - Fix stale paths and references across all documentation
2026-03-11 firmware: draw-wire sign fix and AllSensorsTest pinout aligned with single tests
    - DrawWireTest: negate encoder count so wire extension reports positive distance
    - AllSensorsTest: pinout Theta 32/35, Phi 14/12, Wire 16/17 to match RotaryEncoderTest and DrawWireTest
    - AllSensorsTest: apply same wire sign convention (negate count) for consistent r readout
    Made-with: Cursor
2026-03-11 Before calibration
2026-03-19 WebDashboard Update Expended explanations and added wenscoket alternatives
2026-03-30 Integrate CMD software compatibility across firmware and tools.
    This updates firmware TCP command handling, adds Linux/Windows CMD GUI support and integration docs, and excludes generated .NET build artifacts so pushes stay within GitHub limits.
2026-04-05 Enhance documentation and firmware for WiFi status LED and command validation
    - Added WiFi status LED behavior details to README, including wiring instructions and operational states.
    - Updated CMD software to validate WiFi credentials, returning specific error messages for invalid SSID and password.
    - Improved integration documentation with WiFi credential validation rules and error handling.
    - Adjusted firmware to ensure consistent command responses and error reporting for unknown commands.
    - Reflected changes in the visualizer protocol and updated related Python tools for consistency.
2026-04-05 Ignore legacy CMD GUI publish outputs and remove tracked binaries.
    This keeps generated Windows build artifacts out of version control to reduce repo bloat and avoid push issues caused by oversized binaries.
2026-04-08 08.04.2026 -- CMD Update
    Add hardware documentation for evka_position project
    - Introduced comprehensive Bill of Materials (BOM) detailing components for the double-sided pertinax PCB.
    - Added circuit schematic for the evka_position hardware board, outlining connections and component placements.
    - Provided a PCB layout guide to assist in the design and assembly of the hardware.
    - Included individual hardware test plan for systematic testing of the draw-wire and rotary encoders.
    - Documented integration of CMD protocol for compatibility with third-party GUI, including command handling and system diagnostics.
2026-04-10 10 Nisan CMD Ofis Update documentation and configuration for ESP32-C3 integration
    - Added new environment configuration for button remote testing in `platformio.ini`.
    - Updated `.gitignore` to include additional documentation and legacy files.
    - Enhanced `README.md` and `README_TR.md` with details on the wireless button remote functionality, including GPIO mappings and command actions.
    - Revised calibration documentation to reflect updated GPIO assignments for theta and phi encoders.
    - Removed outdated audit documentation and streamlined references to current performance logs.
    These changes improve the clarity and usability of the project documentation and ensure accurate configuration for
2026-04-13 Update documentation and firmware for OPKON DWEM2 integration
    - Replaced references to the outdated DWE3000 draw-wire encoder with the new OPKON DWEM2 across various documentation files, including README.md, calibration guides, and hardware design documents.
    - Updated firmware constants and calculations to reflect the DWEM2 specifications, including PPR and mm/count values.
    - Enhanced test guides and integration documentation to ensure accurate setup and calibration instructions for the DWEM2 encoder.
    - Adjusted button remote functionality in the firmware and GUI to accommodate new commands for saving and deleting points.
    These changes improve clarity and ensure compatibility with the lates
2026-04-24 Add V2 hardware design documentation with full sourcing audit and corrections
    - Replace CN3767 (lead-acid charger) with BQ24650 3S synchronous buck charger throughout
    - Fix MAX813L DIP-8 pin diagram: was VCC=pin1/GND=pin2, corrected to GND=pin1/VCC=pin8
    - Replace MP2315 (not stocked Turkey) with MP1584EN (direnc.net 26.46 TL) everywhere
    - Fix PIN_ESP_EN=0 definition: EN pin is not addressable as GPIO, replaced with comment
    - Fix MAX485EPA+ VCC: must use 5V_RAIL (min 4.75V), not 3.3V
    - Fix I2C SCL direction: Output -> Bidir open-drain
2026-04-26 V2 power subsystem redesign: remove BQ24650, add Q_BATT active load-sharing
    Three critical architecture flaws fixed across all V2 hardware docs:
    1. Replace Schottky OR-ing (D_EXT/D_BAT) with active IRF4905 MOSFET load-sharing
    (Q_BATT) — adapter now has unconditional priority over 12.6V charged battery.
    Gate circuit: SS14 Schottky (D_GATE) + 100kΩ pull-down (R_G2) + 1N4742A Zener (Z1).
    2. Remove BQ24650 onboard charging entirely — simultaneous charge+load topology
    prevents CC/CV termination, no cell balancing, Turkey sourcing impractical.
2026-04-27 V3 hardware review: fix ADC tap inconsistency, strengthen BMS note, add 12v_tht nav link
    F1 (must-fix): circuit_schematic_v3.md block diagram tapped V12_PROT for GPIO1 ADC
    while section 6 stated BUCK_VIN as the correct default. When adapter is removed,
    V12_PROT collapses to 0V — firmware would see spurious low-battery with V12_PROT tap.
    Moved ADC divider tap to BUCK_VIN in block diagram; removed "or V12_PROT" hedge in
    pin_assignment_v3.md.
    F2 (safety): BMS_3S was qty 0-1 "Recommended if pack remains internal". An internal
2026-04-29 Add 5V PCB v2 design docs for LPKF S63 production
    New directory docs/hardware_design/5v_v2/ with full hardware design for
    the improved 5V board targeting FR4 + LPKF S63 mechanical milling.
    Key improvements over the original pertinax 5v/ design:
    - LTC4412 + AO3401 ideal diode replaces Schottky OR on external path
    (20mV drop vs 350mV; 5V_RAIL stays at 4.98V instead of 4.65V)
    - Dual 5V input: USB-C THT + barrel jack with Schottky OR
2026-04-29 Add hardware design comparison document and presentation
    Create two new deliverables at docs/hardware_design/comparison/:
    - HARDWARE_COMPARISON.md (466 lines): detailed bilingual reference document
    - Section 1: Design evolution timeline (Mermaid)
    - Section 2: 5V→12V migration analysis with TP5100 critical error explanation, 2S LiPo option analysis
    - Section 3: Master comparison table (8 variants)
    - Section 4: Per-variant topology diagrams, specs, strengths, weaknesses
2026-04-30 5V PCB v2 review pass: USB-C Rd, input ESD, pi filter, GPIO12 fix
    Pre-fab review found two functional bugs and several margin issues. Fixed:
    - Add USB-C CC1/CC2 5.1kΩ Rd pulldowns (R_CC1, R_CC2). Without these,
    compliant USB-C sources do not apply VBUS — board would not charge
    from any real USB-C adapter.
    - Move R_GPIO12 (boot strapping pull-down) from divider-input side to
    the 74HC14N output side. The original placement was logically a
2026-06-22 Add 5V v2 PCB design workspace; tidy backups, gitignore KiCad cruft
    - Consolidate 10 .pretty footprint libs into libs/
    - Delete archive/ (superseded versions, nested .history/.git)
    - Thin auto-backup ZIPs to newest 5 per folder
    - Add KiCad ignore rules (backups, locks, autosave, .kicad_prl)
    - Add EVKA_position_v2/README.md folder map
